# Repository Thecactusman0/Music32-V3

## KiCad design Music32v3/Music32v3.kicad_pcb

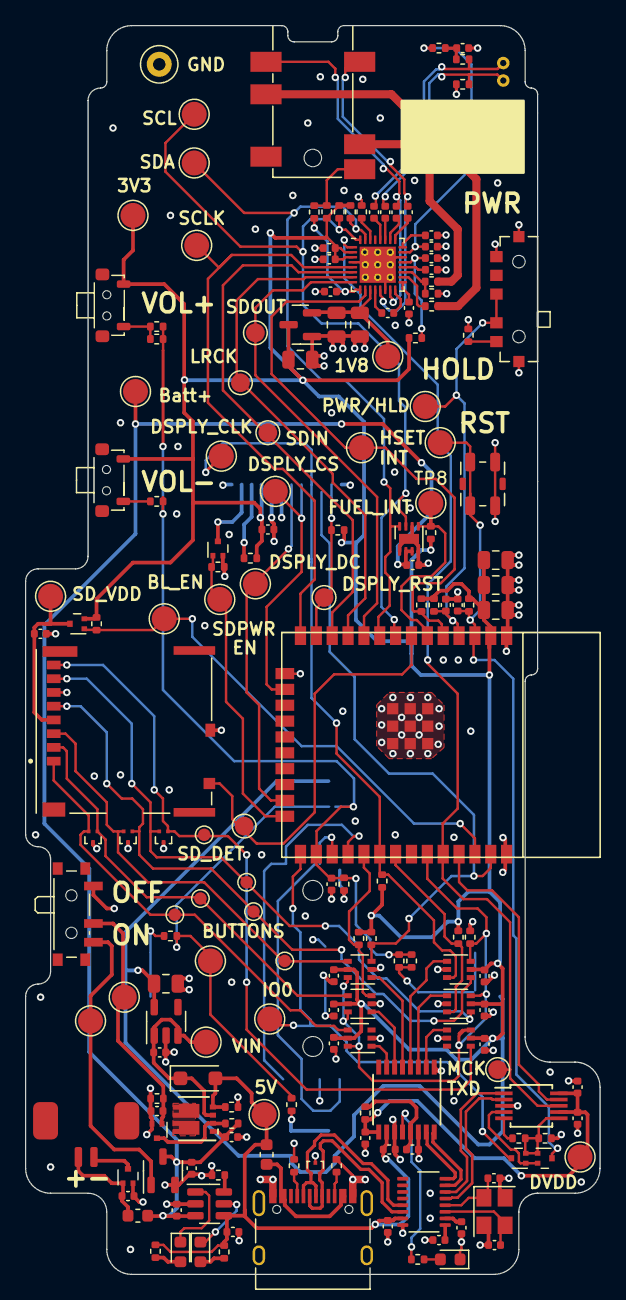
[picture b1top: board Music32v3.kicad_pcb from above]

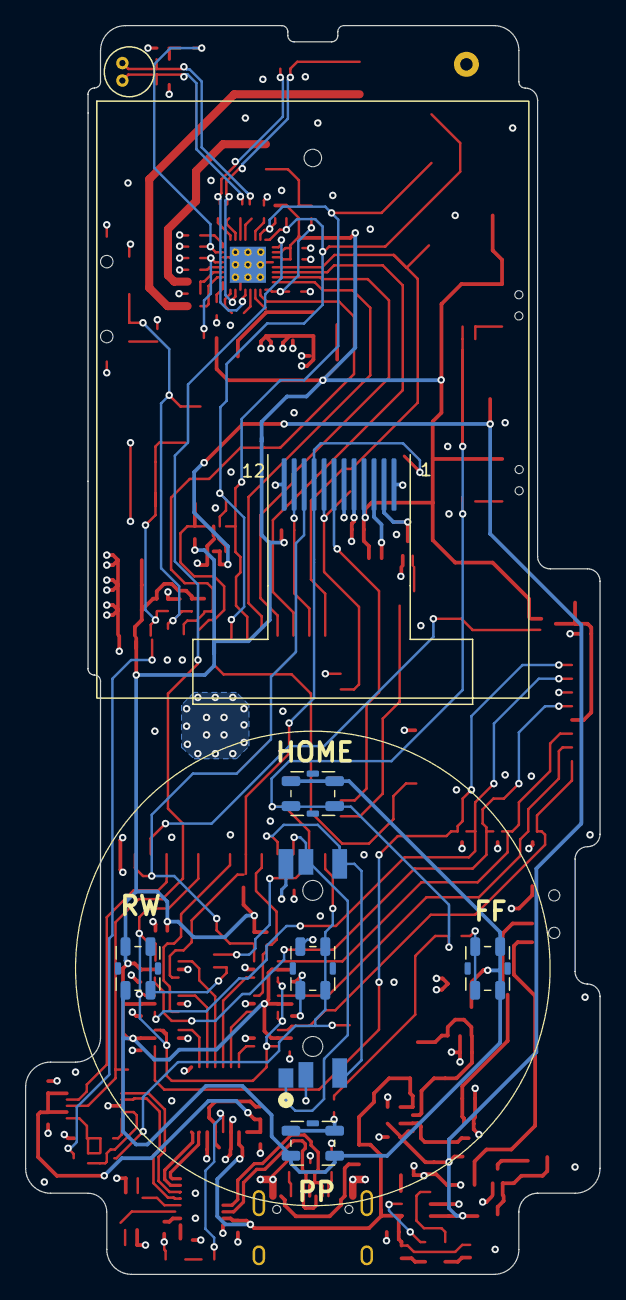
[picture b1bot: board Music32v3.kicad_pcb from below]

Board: 4 copper layers, 46.0 x 100.0 mm, 183 parts (8 on the bottom side), 108 nets.

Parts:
BT1: Battery_Cell; HCZZ0001-2
C1, C3, C8, C10, C13, C17, C18, C21, C22, C23, C24, C25, C26, C27, C30, C31, C33, C36, C37, C38, C39, C40, C41, C43, C44, C45, C46, C47, C48: 1uF; C_0402_1005Metric
C2, C4, C5, C9, C34, C35: 0.1uF; C_0402_1005Metric
C6, C7, C12, C14, C15, C16, C42: 22uf; C_0805_2012Metric
C11, C28, C29, C32, C50: 4.7uF; C_0402_1005Metric
C19, C20: 24pF; C_0402_1005Metric
C49: 47nF; C_0402_1005Metric
D1: DSS34; D_SOD-123F
D2, D3: LED_Small; LED_0603_1608Metric
D4: LED; LED_0603_1608Metric
F1, F2: Polyfuse; Fuse_0603_1608Metric
FB1: 100ohm@100MHz; R_0402_1005Metric
J1: USB_C_Receptacle_USB2.0; U263-163N-4OS1735
J2: Micro_SD_Card_Det1; MOLEX_503398-1892
J3: PJ-316A-6A
MK1: GMI4015P-2C-66db
Q1, Q2, Q3, Q6, Q7: CJ3134K KF; SOT-723
Q4: YJQD30P02A; YJQD30P02A_DFN3.3x3.3
Q5: CJ3139K; SOT-723
R1, R2, R11, R14, R15, R35, R37, R41: 10K; R_0402_1005Metric
R3, R8, R12, R18, R19, R20, R23, R27, R32, R40: 1M; R_0402_1005Metric
R4: 10R; R_0402_1005Metric
R5, R16, R17, R24, R25, R26, R29, R42, R43: 2K; R_0402_1005Metric
R6, R7, R9: 1K; R_0402_1005Metric
R10: 220; R_0402_1005Metric
R13, R21, R22: 5.1K; R_0402_1005Metric
R28, R30, R31, R33: DNP; R_0402_1005Metric
R34: 4K7; R_0402_1005Metric
R36: 0R; R_0402_1005Metric
R38, R39: 220R; R_0402_1005Metric
R44, R45: 33R; R_0402_1005Metric
SW1: Vol+; TSA002A3816B04
SW2: Select; TS3315A
SW3: Vol-; TSA002A3816B04
SW4: PP; TS3315A
SW5: RW; TS3315A
SW6: FF; TS3315A
SW7: HOME; TS3315A
SW8: RESET; TS3315A
SW9: Power; SW_SPDT_PCM12
TP1, TP2, TP3, TP5, TP6, TP7, TP8, TP9, TP10, TP11, TP12, TP14, TP15, TP16, TP17, TP18, TP19, TP20, TP27, TP28, TP29, TP32, TP36: TestPoint; TestPoint_Pad_D2.0mm
TP4, TP30, TP31, TP33, TP34, TP35: TestPoint; TestPoint_Pad_D1.5mm
TP13: TestPoint; TestPoint_Loop_D2.50mm_Drill1.0mm
TP21, TP22, TP23, TP24, TP25, TP26: TestPoint; TestPoint_Pad_D1.0mm
U1: ST7889 2" LCD; TFT020-2_same_side
U2: MAX17048; DFN-8-1EP_2x2mm_P0.5mm_EP0.8x1.6mm
U3: Sk-3393; SK-3393M-G1
U4: SRGP400200; SRGP400200_ALPS
U5: ESP32-WROOM-32E__16MB_; ESP32-WROOM-32E
U6, U19, U21, U22: TPD2EUSB30; Texas_DRT-3
U7: SSP6206-18NR; SOT-23
U8: XC6210B332MR; SOT-23-5
U9: SSP61CC3602MR; SOT-23-3
U10: TP4057; SOT-23-6
U11, U12, U14, U15, U17, U18: SN74LVC1G3157; SOT-363_SC-70-6
U13: SL2.1S
U16: GL823; SSOP-16_3.9x4.9mm_P0.635mm
U20: CH340X; MSOP-10_3x3mm_P0.5mm
U23: ES8327; QFN-32-1EP_4x4mm_P0.4mm_EP2.9x2.9mm_ThermalVias
Y1: 12MHz; Crystal_SMD_3225-4Pin_3.2x2.5mm

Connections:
+1V8: C14.1, C42.1, TP18.1, U7.2 (VO), U23.11 (CPVDD)
+3V3: C1.1, C6.1, C7.1, C12.1, C15.1, C16.1, C22.1, C23.1, C26.1, C27.1, C30.1, C31.1, C36.2, C37.2, Q5.2 (S), R4.1, R8.2, R12.2, R14.1, R15.1, R16.1, R17.1, R27.1, R28.1, R30.1, R31.1, R32.2, R36.1, R37.1, R40.1, SW1.2, SW3.2, SW4.2, SW5.2, SW6.2, SW7.2, TP20.1, U1.4 (VCC), U5.2 (3V3), U7.3 (VI), U8.5 (VOUT), U11.5 (VCC), U12.5 (VCC), U14.5 (VCC), U15.5 (VCC), U17.5 (VCC), U18.5 (VCC), U23.2 (DVDD), U23.3 (PVDD)
/Codec/HP_Detect: J3.TN, R38.1, R40.2
/Codec/M1+: C46.1, J3.S, U23.15 (GMS1)
/Codec/M1-: C47.1, J3.R2, U23.13 (GMS0)
/Codec/M2+: C44.1, MK1.2 (+), R42.2
/Codec/M2-: C45.1, MK1.1 (-), R43.1
/PSU/PSEN_DRIVE: Q3.3 (D), Q4.2 (G2), R19.1
/PSU/PSEN_GATE: SW9.3 (C), TP19.1, U9.1 (Out)
/PSU/VIN: C11.1, D1.1 (K), Q4.3 (S2), TP17.1, U8.1 (VIN), U8.3 (CE)
ADCVREF: C38.2, R39.1, U23.23 (ADCVREF)
BATT+: C3.1, C8.1, C13.1, C18.1, F2.2, Q4.1 (S2), R19.2, TP14.1, U2.2 (CELL), U2.3 (Vdd), U9.3 (Vin), U10.3 (BAT)
BL_EN: Q1.1 (G), R3.2, TP2.1, U5.24 (IO2)
BUTTONS: C2.1, R1.1, R2.1, R5.2, R6.2, R7.2, R9.2, R10.2, R11.2, SW7.1, TP7.1, U5.26 (IO4)
CLK_RD: U16.4 (CLK), U18.1 (B2)
CLK_SD: J2.5 (CLK), TP24.1, U18.4 (A), U22.1 (D+)
CLK_UC: R31.2, TP5.1, U1.9 (SCL), U5.30 (IO18), U18.3 (B1)
CMD_RD: U16.5 (CMD), U17.1 (B2)
CMD/MOSI_SD: J2.3 (CMD), TP23.1, U17.4 (A), U22.2 (D-)
CS_SD: R27.2, U5.29 (IO5), U14.3 (B1)
D+: J1.A6 (D+), J1.B6 (D+), U6.2 (D-), U13.6 (UDP)
D-: J1.A7 (D-), J1.B7 (D-), U6.1 (D+), U13.5 (UDM)
DAT0_RD: U15.1 (B2), U16.3 (D0)
DAT0/MISO_SD: J2.7 (DAT0), TP25.1, U15.4 (A), U21.2 (D-)
DAT1_RD: U12.1 (B2), U16.2 (D1)
DAT1_SD: J2.8 (DAT1), TP26.1, U12.4 (A), U21.1 (D+)
DAT2_RD: U11.1 (B2), U16.7 (D2)
DAT2_SD: J2.1 (DAT2), TP21.1, U11.4 (A), U19.2 (D-)
DAT3_RD: U14.1 (B2), U16.6 (D3)
DAT3/CS_SD: J2.2 (DAT3/CD), TP22.1, U14.4 (A), U19.1 (D+)
DISPLAY_CS: TP6.1, U1.8 (CS), U5.16 (IO13)
DISPLAY_DC: TP3.1, U1.7 (D/C), U5.23 (IO15)
DISPLAY_RESET: R8.1, TP4.1, U1.11 (RESET), U5.13 (IO14)
DVDD: C29.1, C34.1, C35.1, FB1.2, TP29.1, U16.9 (DVDD), U20.7 (VCC), U20.10 (V3)
EN: C5.1, Q7.3 (D), R15.2, SW8.2, TP10.1, U5.3 (EN)
ENCODER_1: U4.1, U4.5 (1), U5.27 (IO16)
ENCODER_2: U4.3 (2), U4.4 (2), U5.28 (IO17)
FUEL_INT: R12.1, TP8.1, U2.5 (ALRT), U5.6 (IO34)
GND: C1.2, C2.2, C3.2, C4.2, C5.2, C6.2, C7.2, C8.2, C9.2, C10.2, C11.2, C12.2, C13.2, C14.2, C15.2, C16.2, C17.2, C18.2, C19.1, C20.1, C21.2, C22.2, C23.2, C24.2, C25.2, C26.2, C27.2, C28.2, C29.2, C30.2, C31.2, C32.2, C33.2, C34.2, C35.2, C36.1, C37.1, C38.1, C39.1, C40.1, C41.1, C42.2, C48.1, C49.1, C50.1, D4.1 (K), J1.A1 (GND), J1.A12 (GND), J1.B1 (GND), J1.B12 (GND), J1.S1 (SHIELD), J2.6 (VSS), J2.10 (SHIELD), Q1.2 (S), Q2.2 (S), Q3.2 (S), R3.1, R11.1, R13.1, R18.1, R20.1, R21.2, R22.2, R23.1, R26.2, R34.2, R35.1, R41.2, R43.2, SW2.2, SW8.1, SW9.1 (A), TP13.1, U1.1 (GND), U1.5 (GND), U1.6 (GND), U1.12 (GND), U2.1 (CTG), U2.4 (GND), U2.6 (QSTRT), U2.9 (EP), U3.1, U3.6,7, U4.2 (C), U4.6 (GND), U5.1 (GND), U5.15 (GND), U5.38 (GND), U6.3 (GND), U7.1 (GND), U8.2 (GND), U9.2 (Gnd), U10.2 (GND), U11.2 (GND), U12.2 (GND), U13.8 (VSS), U14.2 (GND), U15.2 (GND), U16.1 (GND), U16.11 (GPIO), U16.14 (GND), U17.2 (GND), U18.2 (GND), U19.3 (GND), U20.3 (GND), U21.3 (GND), U22.3 (GND), U23.4 (DGND), U23.14 (CPGND), U23.22 (AGND), U23.33 (PAD), Y1.2, Y1.4
HEADSET_INT: R37.2, TP36.1, U5.5 (SENSOR_VN), U23.10 (INOUT)
IO0: Q6.3 (D), SW2.1, TP1.1, U5.25 (IO0)
LRCK: TP34.1, U5.11 (IO26), U23.7 (LRCK)
MCLK_TXD: TP31.1, U5.34 (RXD0), U20.8 (TXD), U23.1 (MCLK)
MISO_UC: R28.2, U5.31 (IO19), U15.3 (B1)
MOSI_UC: R30.2, U1.10 (SDA), U5.37 (IO23), U17.3 (B1)
unnamed: BT1.2 (+), C10.1, F2.1, Q2.1 (G)
unnamed: C50.2, R39.2, R42.1
unnamed: D2.2 (A), R24.2
unnamed: D2.1 (K), U10.5 (STDBY)
unnamed: D3.2 (A), R25.2
unnamed: D3.1 (K), U10.1 (CHRG)
unnamed: D4.2 (A), R29.2
unnamed: F1.1, J1.A4 (VBUS), J1.A9 (VBUS), J1.B4 (VBUS), J1.B9 (VBUS)
unnamed: J1.A5 (CC1), R21.1
unnamed: J1.B5 (CC2), R22.1
unnamed: C33.1, J2.4 (VDD), Q5.3 (D), TP28.1
unnamed: J3.R1, R44.2
unnamed: J3.T, R45.2
unnamed: Q1.3 (D), U1.2 (LEDK)
unnamed: BT1.1, Q2.3 (D)
unnamed: C9.1, Q3.1 (G), R20.2, SW9.2 (B), TP15.1
unnamed: Q4.5 (D2), Q4.6 (D2), Q4.7 (D2), Q4.8 (D2)
unnamed: Q6.1 (G), Q7.2 (S), U20.4 (RTS)
unnamed: Q6.2 (S), Q7.1 (G), R33.2, R34.1, U20.6 (TNOW/DTR)
unnamed: R1.2, R2.2, SW1.1
unnamed: R5.1, SW3.1
unnamed: R6.1, SW4.1
unnamed: R7.1, R9.1, SW5.1
unnamed: R10.1, SW6.1
unnamed: R13.2, U3.5
unnamed: R4.2, U1.3 (LEDA)
unnamed: R26.1, U10.6 (PROG)
unnamed: C25.1, U13.10 (VDD18)
unnamed: C24.1, U13.9 (VDD33)
unnamed: C20.2, U13.12 (XIN), Y1.1
unnamed: C19.2, U13.11 (XOUT), Y1.3
unnamed: C32.1, FB1.1, U16.13 (AVDD)
unnamed: R29.1, U16.12 (LED)
unnamed: R33.1, U20.5 (CTS)
unnamed: C41.2, R36.2, U23.21 (AVDD)
unnamed: R35.2, U23.30 (CE)
unnamed: C43.1, U23.16 (CPBOT)
unnamed: C43.2, U23.12 (CPTOP)
unnamed: C48.2, U23.17 (CPVSSP)
unnamed: C39.2, U23.20 (DACVREF)
unnamed: C49.2, R38.2, U23.9 (HEADSET)
unnamed: R41.1, R45.1, U23.19 (LOUT)
unnamed: C47.2, U23.25 (MIC1N)
unnamed: C46.2, U23.26 (MIC1P)
unnamed: C45.2, U23.27 (MIC2N)
unnamed: C44.2, U23.28 (MIC2P)
unnamed: R44.1, U23.18 (ROUT)
unnamed: C40.2, U23.24 (VMID)
PWR/HOLD: C4.1, R14.2, TP9.1, U3.3,4, U5.4 (SENSOR_VP)
RXD: U5.35 (TXD0), U20.9 (RXD)
SCL: R16.2, TP11.1, U2.7 (SCL), U5.8 (IO32), U23.32 (CCLK)
SCLK: TP32.1, U5.14 (IO12), U23.5 (SCLK)
SDA: R17.2, TP12.1, U2.8 (SDA), U5.9 (IO33), U23.31 (CDATA)
SDIN: TP33.1, U5.12 (IO27), U23.6 (SDIN)
SDOUT: TP35.1, U5.10 (IO25), U23.8 (SDOUT)
SD_D+: U13.16 (DP3), U16.15 (D+)
SD_D-: U13.15 (DM3), U16.16 (D-)
SD_DETECT: J2.9 (DET), TP30.1, U5.7 (IO35)
SD_PWR_EN: Q5.1 (G), R32.1, TP27.1, U5.36 (IO22)
SD_SELECT: R18.2, U5.33 (IO21), U11.6 (S), U12.6 (S), U14.6 (S), U15.6 (S), U17.6 (S), U18.6 (S)
UART_D+: U13.14 (DP4), U20.1 (D+)
UART_D-: U13.13 (DM4), U20.2 (D-)
VBUS: C17.1, C21.1, C28.1, D1.2 (A), F1.2, Q4.4 (G2), R23.2, R24.1, R25.1, TP16.1, U10.4 (VCC), U13.7 (VDD5), U16.10 (VBUS)

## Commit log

2023-11-20 Init
2023-11-21 MCU and PSU
    MCU and PSU Schem started
2023-11-23 PSU update
2023-11-23 SD card and usb and power
2023-11-25 Schematic
2023-11-25 Reorganised
2023-11-25 Auto programming
2023-11-27 PCB outline
2023-11-29 Board setup
2023-11-29 Button placement fix
2023-12-03 pcb done
2023-12-09 Cleaning up file
2023-12-11 pdf schematic
2023-12-18 created 3d files
2023-12-19 remade the encoder 3d model
    made it not mesh
2023-12-19 Pcb changes
2023-12-19 Fixed 3d models
2023-12-19 Fixed resistor
